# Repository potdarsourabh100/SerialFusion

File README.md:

# 🚀 SerialFusion

*Universal Isolated USB-to-UART / ESP32 Programmer / RS485 / RS232 Converter*

---

## 📖 Overview

**SerialFusion** is a professional-grade isolated USB communication and programming tool designed for embedded engineers, makers, students, and industrial automation developers.

The board combines multiple serial communication interfaces into a single compact device:

* USB ↔ UART (TTL/CMOS)
* ESP32 Auto Programmer
* USB ↔ RS485 Converter
* USB ↔ RS232 Converter

At its core is the reliable **CH340K USB-UART bridge**, combined with digital isolation, isolated power, industrial-grade transceivers, and ESP32 auto-programming support.

Unlike typical USB-TTL adapters, SerialFusion provides electrical isolation, industrial communication interfaces, visual status indicators, and user-friendly connectors suitable for both development and field deployment.

---

## ✨ Features

### USB-C Connectivity

* USB Type-C interface
* ESD-protected USB data lines
* Modern reversible connector
* Bus-powered operation

### Isolated UART Interface

* CH340K USB-UART bridge
* ISO7721 digital isolation
* Complete galvanic isolation between PC and target hardware
* Protection against ground loops and industrial noise

### Isolated Power Supply

* MEJ1S0505SC isolated DC-DC converter
* Independent isolated target-side supply
* Low-noise 3.3V regulation using MIC5219

### ESP32 Programming Support

* Automatic bootloader entry
* RTS → EN control
* DTR → IO0 control
* Compatible with ESP-IDF
* Compatible with Arduino IDE
* Manual BOOT and RESET pushbuttons

### RS485 Interface

* ISL3172E industrial RS485 transceiver
* Half-duplex communication
* Selectable onboard 120Ω termination resistor
* Suitable for:

  * Modbus RTU
  * EST-RBUS16
  * Custom industrial protocols
  * Multi-drop networks

### RS232 Interface

* MAX3232 RS232 transceiver
* Standard DB9 connector
* Full voltage-level conversion
* Legacy equipment compatibility

### Debugging Features

* Dedicated UART debug header
* TX activity LED
* RX activity LED
* Power indicator LED
* Clearly labeled pinout

### User-Friendly Design

* Color-coded silkscreen labels
* Compact PCB layout
* Ground-pour optimized routing
* Easy access connectors
* Professional assembly-friendly footprint selection

---

## 🔌 Interfaces

### ESP32 Programming Header

| Pin | Function     |
| --- | ------------ |
| TX  | UART TX      |
| RX  | UART RX      |
| EN  | ESP32 Reset  |
| IO0 | ESP32 Boot   |
| 3V3 | Target Power |
| GND | Ground       |

Supports automatic firmware upload without manual button presses.

---

### UART Debug Header

| Pin | Function |
| --- | -------- |
| TX  | UART TX  |
| RX  | UART RX  |
| 3V3 | Supply   |
| GND | Ground   |

Ideal for debugging microcontrollers and embedded systems.

---

### RS485 Connector

| Pin | Function |
| --- | -------- |
| A   | RS485 A  |
| B   | RS485 B  |

Features selectable onboard termination resistor.

---

### RS232 Connector

Standard DB9 serial interface for legacy equipment and industrial devices.

---

## 🏗 Architecture

PC USB

↓

USB-C

↓

CH340K USB-UART

↓

ISO7721 Isolation

↓

┌─────────────┬─────────────┬─────────────┐

│ UART Debug │ ESP32 Prog │ Industrial │

│ Interface │ Interface │ Interfaces │

│ │ │ │

│ │ │ ├── RS485

│ │ │ └── RS232

└─────────────┴─────────────┴─────────────┘

---

## ⚡ Power Architecture

USB 5V

↓

MEJ1S0505SC

(Isolated DC-DC)

↓

MIC5219-3.3

↓

Isolated 3.3V Rail

This architecture provides protection against:

* Ground loops
* Industrial noise
* USB port damage
* Common-mode voltage issues

---

## 🧪 Typical Applications

### Embedded Development

* ESP32 programming
* STM32 debugging
* RP2040 development
* AVR programming
* UART monitoring

### Industrial Automation

* Modbus RTU testing
* PLC communication
* RS485 network diagnostics
* Protocol development
* Field commissioning

### Education & Learning

* Serial communication experiments
* Embedded systems labs
* Industrial communication training

---

## 🔥 Project Status

Current Stage:

**Prototype Validation**

Roadmap:

* [x] Schematic Design
* [x] PCB Layout
* [ ] Prototype Assembly
* [ ] Functional Testing
* [ ] Firmware Validation
* [ ] Production Release

---

## ❤️ Author

### EmbSysTech Innovations

**Bytes of Innovations**

Designed with passion for Embedded Systems, Industrial Electronics, and Open Hardware.

---

## ⭐ Support

If you like this project:

⭐ Star the repository

🍴 Fork the project

📢 Share with makers, students, and engineers

☕ Help spread the word about open hardware development

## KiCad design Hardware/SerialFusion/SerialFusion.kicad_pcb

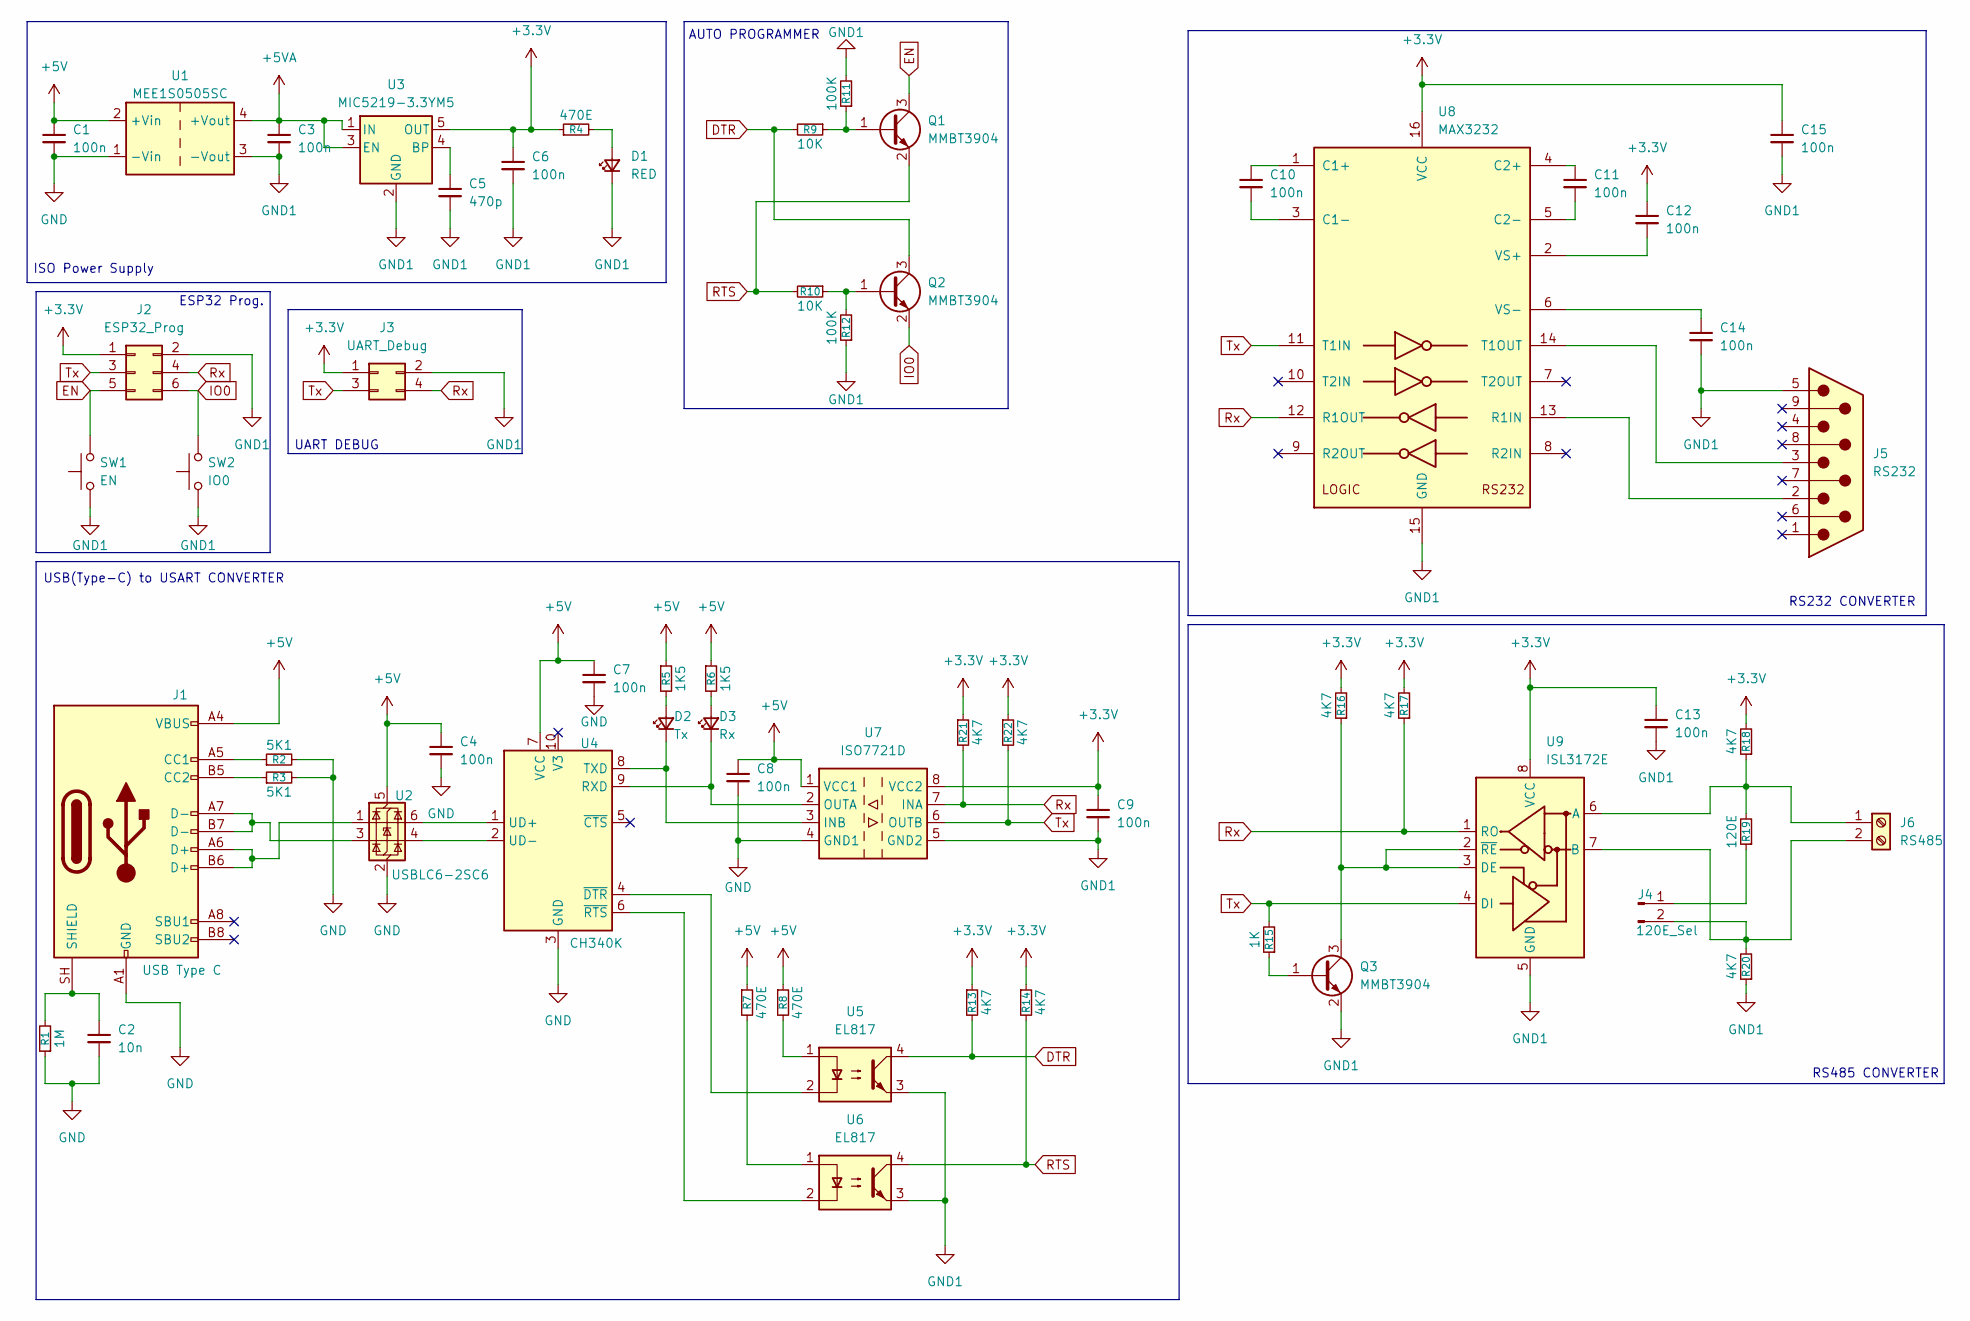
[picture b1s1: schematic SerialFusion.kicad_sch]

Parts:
C1, C3, C4, C6, C7, C8, C9, C10, C11, C12, C13, C14, C15: 100n; C_1206_3216Metric_Pad1.33x1.80mm_HandSolder
C2: 10n; C_1206_3216Metric_Pad1.33x1.80mm_HandSolder
C5: 470p; C_1206_3216Metric_Pad1.33x1.80mm_HandSolder
D1: RED; D_1206_3216Metric_Pad1.42x1.75mm_HandSolder
D2: Tx; D_1206_3216Metric_Pad1.42x1.75mm_HandSolder
D3: Rx; D_1206_3216Metric_Pad1.42x1.75mm_HandSolder
J1: USB Type C; USB_C_Receptacle_GCT_USB4105-xx-A_16P_TopMnt_Horizontal
J2: ESP32_Prog; PinHeader_2x03_P2.54mm_Vertical
J3: UART_Debug; PinHeader_2x02_P2.54mm_Vertical
J4: 120E_Sel; PinHeader_1x02_P2.54mm_Vertical
J5: RS232; DSUB-9_Socket_Horizontal_P2.77x2.84mm_EdgePinOffset14.56mm_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
J6: RS485; TerminalBlock_Phoenix_MKDS-1,5-2-5.08_1x02_P5.08mm_Horizont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
Q1, Q2, Q3: MMBT3904; SOT-23
R1: 1M; R_1206_3216Metric_Pad1.30x1.75mm_HandSolder
R2, R3: 5K1; R_1206_3216Metric_Pad1.30x1.75mm_HandSolder
R4, R7, R8: 470E; R_1206_3216Metric_Pad1.30x1.75mm_HandSolder
R5, R6: 1K5; R_1206_3216Metric_Pad1.30x1.75mm_HandSolder
R9, R10: 10K; R_1206_3216Metric_Pad1.30x1.75mm_HandSolder
R11, R12: 100K; R_1206_3216Metric_Pad1.30x1.75mm_HandSolder
R13, R14, R16, R17, R18, R20, R21, R22: 4K7; R_1206_3216Metric_Pad1.30x1.75mm_HandSolder
R15: 1K; R_1206_3216Metric_Pad1.30x1.75mm_HandSolder
R19: 120E; R_1206_3216Metric_Pad1.30x1.75mm_HandSolder
SW1: EN; SW_SPST_CK_RS282G05A3
SW2: IO0; SW_SPST_CK_RS282G05A3
U1: MEE1S0505SC; Converter_DCDC_Murata_MEE1SxxxxSC_THT
U2: USBLC6-2SC6; SOT-23-6
U3: MIC5219-3.3YM5; SOT-23-5
U4: CH340K; SSOP-10-1EP_3.9x4.9mm_P1mm_EP2.1x3.3mm
U5, U6: EL817; DIP-4_W7.62mm_SMDSocket_SmallPads
U7: ISO7721D; SOIC-8_3.9x4.9mm_P1.27mm
U8: MAX3232; SOIC-16W_5.3x10.2mm_P1.27mm
U9: ISL3172E; SOIC-8_3.9x4.9mm_P1.27mm

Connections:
+3.3V: C6.1, C9.1, C12.1, C13.1, C15.1, J2.1, J3.1, R4.1, R13.1, R14.1, R16.2, R17.2, R18.2, R21.1, R22.1, U3.5 (OUT), U7.8 (VCC2), U8.16 (VCC), U9.8 (VCC)
+5V: C1.1, C4.1, C7.1, C8.1, J1.A4 (VBUS), J1.A9 (VBUS), J1.B4 (VBUS), J1.B9 (VBUS), R5.1, R6.1, R7.1, R8.1, U1.2 (+Vin), U2.5 (VBUS), U4.7 (VCC), U7.1 (VCC1)
+5VA: C3.1, U1.4 (+Vout), U3.1 (IN), U3.3 (EN)
DTR: Q2.3 (C), R9.2, R13.2, U5.4
EN: J2.5, Q1.3 (C), SW1.2
GND: C1.2, C2.2, C4.2, C7.2, C8.2, J1.A1 (GND), J1.A12 (GND), J1.B1 (GND), J1.B12 (GND), R1.1, R2.2, R3.2, U1.1 (-Vin), U2.2 (GND), U4.3 (GND), U4.11 (GND), U7.4 (GND1)
GND1: C3.2, C5.2, C6.2, C9.2, C13.2, C14.2, C15.2, D1.1 (K), J2.2, J3.2, J5.5, Q3.2 (E), R11.2, R12.1, R20.1, SW1.1, SW2.1, U1.3 (-Vout), U3.2 (GND), U5.3, U6.3, U7.5 (GND2), U8.15 (GND), U9.5 (GND)
IO0: J2.6, Q2.2 (E), SW2.2
unnamed: D1.2 (A), R4.2
unnamed: D2.2 (A), R5.2
unnamed: D2.1 (K), U4.8 (TXD), U7.3 (INB)
unnamed: D3.2 (A), R6.2
unnamed: D3.1 (K), U4.9 (RXD), U7.2 (OUTA)
unnamed: J1.A5 (CC1), R2.1
unnamed: J1.B5 (CC2), R3.1
unnamed: J1.A6 (D+), J1.B6 (D+), U2.1 (I/O1)
unnamed: J1.A7 (D-), J1.B7 (D-), U2.3 (I/O2)
unnamed: C2.1, J1.SH (SHIELD), R1.2
unnamed: J4.1, R19.1
unnamed: J4.2, J6.2, R20.2, U9.7 (B)
unnamed: J6.1, R18.1, R19.2, U9.6 (A)
unnamed: Q1.1 (B), R9.1, R11.1
unnamed: Q2.1 (B), R10.1, R12.2
unnamed: Q3.1 (B), R15.1
unnamed: Q3.3 (C), R16.1, U9.2 (~RE), U9.3 (DE)
unnamed: R7.2, U6.1
unnamed: R8.2, U5.1
unnamed: C5.1, U3.4 (BP)
unnamed: U2.6 (I/O1), U4.1 (UD+)
unnamed: U2.4 (I/O2), U4.2 (UD-)
unnamed: U4.4 (~DTR), U5.2
unnamed: U4.6 (~RTS), U6.2
unnamed: C10.1, U8.1 (C1+)
unnamed: C10.2, U8.3 (C1-)
unnamed: C11.1, U8.4 (C2+)
unnamed: C11.2, U8.5 (C2-)
unnamed: J5.2, U8.13 (R1IN)
unnamed: J5.3, U8.14 (T1OUT)
unnamed: C12.2, U8.2 (VS+)
unnamed: C14.1, U8.6 (VS-)
RTS: Q1.2 (E), R10.2, R14.2, U6.4
Rx: J2.4, J3.4, R17.1, R21.2, U7.7 (INA), U8.12 (R1OUT), U9.1 (RO)
Tx: J2.3, J3.3, R15.2, R22.2, U7.6 (OUTB), U8.11 (T1IN), U9.4 (DI)

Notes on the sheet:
RS485 CONVERTER
AUTO PROGRAMMER
ISO Power Supply
USB(Type-C) to USART CONVERTER
ESP32 Prog.
UART DEBUG
RS232 CONVERTER

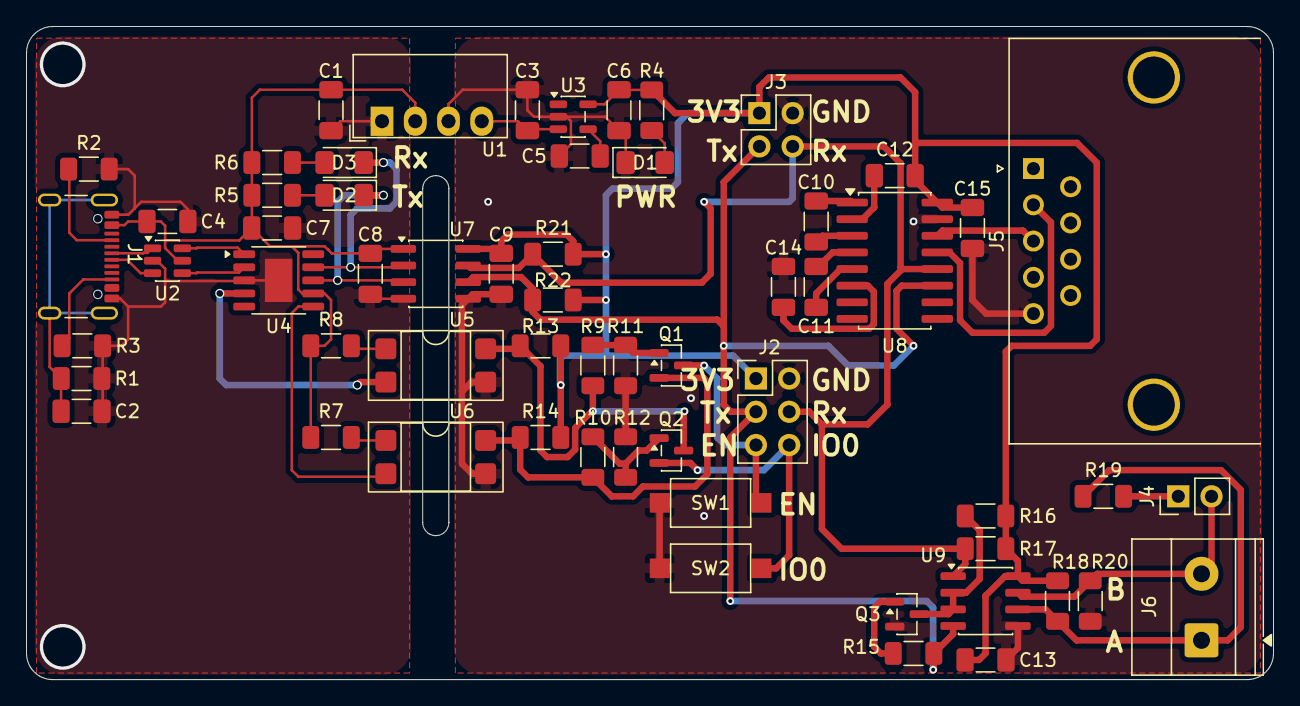
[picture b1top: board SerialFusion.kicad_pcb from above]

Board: 2 copper layers, 95.3 x 49.9 mm, 60 parts (0 on the bottom side), 43 nets.

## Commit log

2026-05-08 Initial release
2026-05-14 Intermediate release with Schematic in progress as well as README.md is under changes
2026-06-10 First stage design for Rev A is completed & files updated
